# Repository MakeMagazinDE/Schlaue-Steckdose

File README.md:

Maker Media GmbH

***

# Schlaue Steckdose

**Steckdosen, die man über das Handy schalten kann, sind nichts Neues. Auch gibt es Mehrfachsteckdosen, die nur Strom verteilen, wenn ein bestimmtes Gerät an ist. Das alles ist unserem Autor nicht genug und deshalb hat er sich eine Steckdosenleiste gebaut, die Geräte abhängig von seiner Anwesenheit mit Strom versorgt oder bei bestimmten Temperaturen die Heizung regelt.**

Der vollständige Artikel zum Projekt steht in der **[Make-Ausgabe 5/23 ab Seite 54](https://www.heise.de/select/make/2023/5)**.

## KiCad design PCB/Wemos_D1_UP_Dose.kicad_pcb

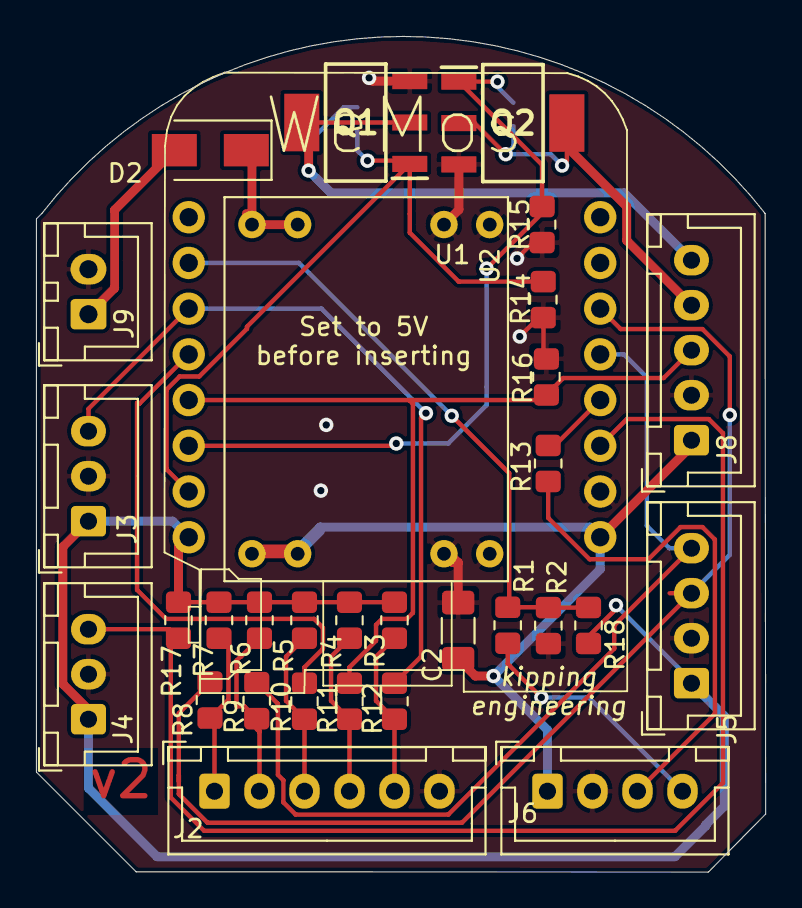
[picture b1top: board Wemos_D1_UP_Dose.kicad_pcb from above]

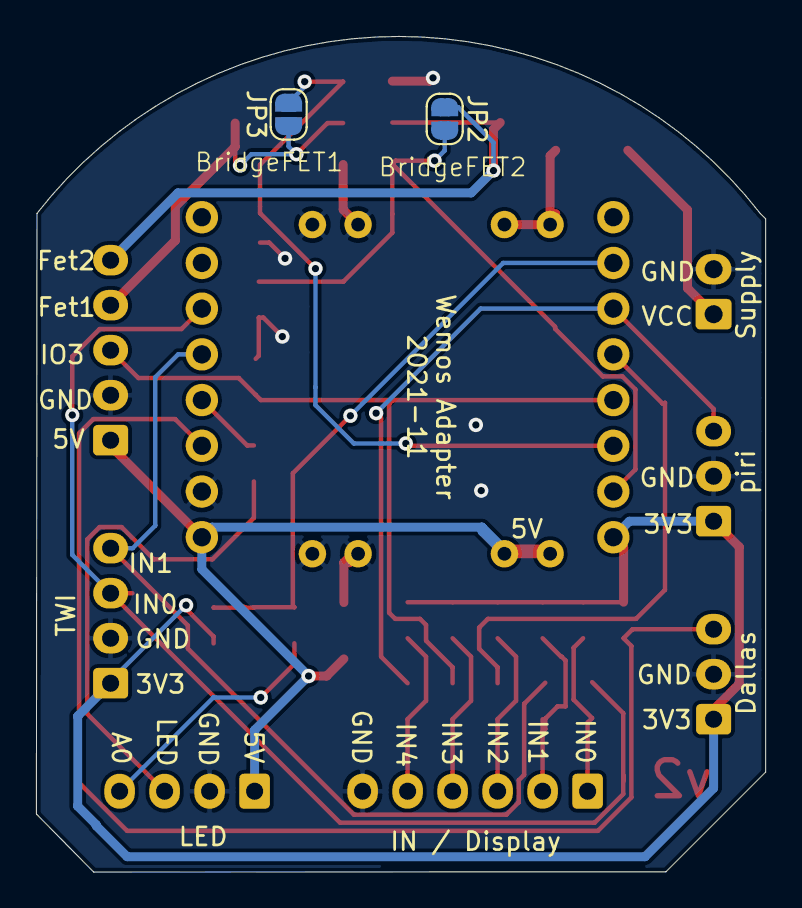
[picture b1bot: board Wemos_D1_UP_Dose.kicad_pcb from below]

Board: 2 copper layers, 40.5 x 46.4 mm, 33 parts (2 on the bottom side), 24 nets.

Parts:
C2: 1µ; C_1206_3216Metric_Pad1.33x1.80mm_HandSolder
D2: US1G; D_SMA
J2: IN_0-4; JST_XH_B6B-XH-A_1x06_P2.50mm_Vertical
J3: IN4_PIRI; JST_XH_B3B-XH-A_1x03_P2.50mm_Vertical
J4: Dallas; JST_XH_B3B-XH-A_1x03_P2.50mm_Vertical
J5: TWI; JST_XH_B4B-XH-A_1x04_P2.50mm_Vertical
J6: LED; JST_XH_B4B-XH-A_1x04_P2.50mm_Vertical
J8: OUT_FET; JST_XH_B5B-XH-A_1x05_P2.50mm_Vertical
J9: POWER; JST_XH_B2B-XH-A_1x02_P2.50mm_Vertical
JP2, JP3: Jumper_NO_Small; SolderJumper-2_P1.3mm_Open_RoundedPad1.0x1.5mm
Q1, Q2: BUK7880-55A_CUX; SOT230P700X180-4N
R1: 100k; R_0805_2012Metric_Pad1.20x1.40mm_HandSolder
R2, R3, R4, R5, R6, R7, R14, R15, R17, R18: 4k7; R_0805_2012Metric_Pad1.20x1.40mm_HandSolder
R8, R9, R10, R11, R12: 1k; R_0805_2012Metric_Pad1.20x1.40mm_HandSolder
R13, R16: 100; R_0805_2012Metric_Pad1.20x1.40mm_HandSolder
U1: WeMos_mini; D1_mini_board
U2: DCDC_1A_Module; DCDC_1A_module

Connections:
+3V3: J3.1, J4.1, J5.1, R3.1, R4.1, R5.1, R6.1, R7.1, R17.2, R18.2, U1.16
+5V: C2.1, J6.1, J8.1, U1.1, U2.2
A0: R1.2, R2.1, R18.1, U1.10
DALLAS: J4.3, R17.1, U1.3
FET_1: JP3.2, Q2.1, R15.1, U1.14
FET_2: JP2.2, Q1.1, R14.1, U1.15
GND: C2.2, J2.6, J3.2, J4.2, J5.2, J6.2, J8.2, J9.2, Q1.3, Q2.3, R2.2, R14.2, R15.2, R16.2, U1.2, U2.3
IN_0: J5.3, R8.2, U1.6
IN_1: J5.4, R9.2, U1.5
IN_2: R10.2, U1.12
IN_3: J8.3, R11.2, R16.1, U1.13
IN_4: J3.3, R12.2, U1.11
LED: R13.2, U1.4
unnamed: D2.1, U2.1
unnamed: D2.2, J9.1
unnamed: J2.1, R7.2, R8.1
unnamed: J2.2, R6.2, R9.1
unnamed: J2.3, R5.2, R10.1
unnamed: J2.4, R4.2, R11.1
unnamed: J2.5, R3.2, R12.1
unnamed: J6.3, R13.1
unnamed: J6.4, R1.1
unnamed: J8.4, JP3.1, Q2.2, Q2.4
unnamed: J8.5, JP2.1, Q1.2, Q1.4

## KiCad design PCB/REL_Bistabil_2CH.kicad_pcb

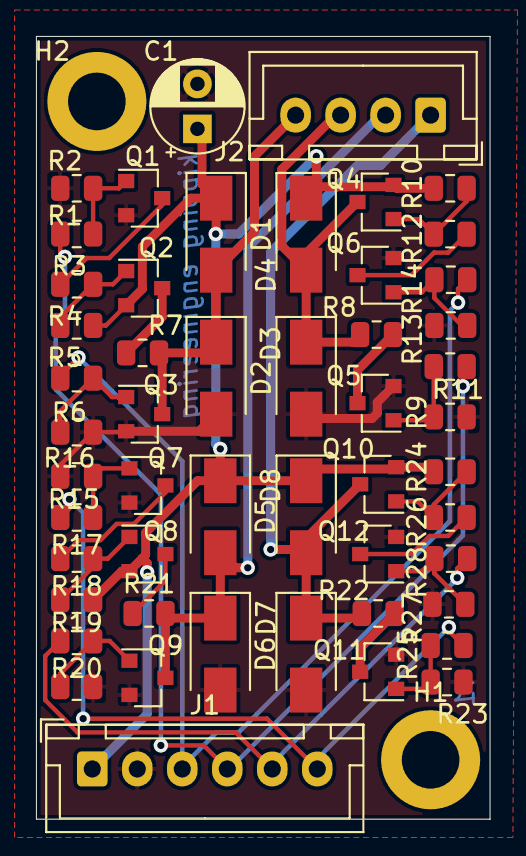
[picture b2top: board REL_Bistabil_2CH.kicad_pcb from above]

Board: 2 copper layers, 25.2 x 43.5 mm, 53 parts (0 on the bottom side), 30 nets.

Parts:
C1: C; CP_Radial_D5.0mm_P2.50mm
D1, D2, D3, D4, D5, D6, D7, D8: US1G; D_SMA
H1, H2: MountingHole; MountingHole_3.2mm_M3_ISO14580_Pad
J1: Conn_01x06_Male; JST_XH_B6B-XH-A_1x06_P2.50mm_Vertical
J2: Conn_01x04_Male; JST_XH_B4B-XH-A_1x04_P2.50mm_Vertical
Q1, Q3, Q5, Q6, Q7, Q9, Q11, Q12: BC817; SOT-23
Q2, Q4, Q8, Q10: BC807; SOT-23
R1, R14, R15, R28: 4k7; R_0805_2012Metric
R2, R4, R6, R9, R10, R13, R16, R18, R20, R23, R24, R27: 100k; R_0805_2012Metric
R3, R12, R17, R26: 1k; R_0805_2012Metric
R5, R11, R19, R25: 200; R_0805_2012Metric
R7, R8, R21, R22: 100; R_0805_2012Metric

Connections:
+12V: C1.1, D1.1, D4.1, D5.1, D8.1, J1.1, Q2.2, Q4.2, Q8.2, Q10.2, R4.1, R10.1, R18.1, R24.1
/h-bridge/REL_R: D3.1, D4.2, J2.3, Q4.3, R8.1
/h-bridge/REL_S: D1.2, D2.1, J2.4, Q3.3, R7.2
/h-bridge/Reset: J1.4, R1.2, R11.2
/h-bridge/Set: J1.3, R5.2, R14.2
/sheet623AF816/REL_R: D7.1, D8.2, J2.1, Q10.3, R22.1
/sheet623AF816/REL_S: D5.2, D6.1, J2.2, Q9.3, R21.2
/sheet623AF816/Reset: J1.6, R15.2, R25.2
/sheet623AF816/Set: J1.5, R19.2, R28.2
GND: C1.2, D2.2, D3.2, D6.2, D7.2, J1.2, Q1.2, Q3.2, Q5.2, Q6.2, Q7.2, Q9.2, Q11.2, Q12.2, R2.2, R6.1, R9.1, R13.2, R16.2, R20.1, R23.1, R27.2
unnamed: Q1.1, R1.1, R2.1
unnamed: Q1.3, R3.2
unnamed: Q2.1, R3.1, R4.2
unnamed: Q2.3, R7.1
unnamed: Q3.1, R5.1, R6.2
unnamed: Q4.1, R10.2, R12.1
unnamed: Q5.1, R9.2, R11.1
unnamed: Q5.3, R8.2
unnamed: Q6.1, R13.1, R14.1
unnamed: Q6.3, R12.2
unnamed: Q7.1, R15.1, R16.1
unnamed: Q7.3, R17.2
unnamed: Q8.1, R17.1, R18.2
unnamed: Q8.3, R21.1
unnamed: Q9.1, R19.1, R20.2
unnamed: Q10.1, R24.2, R26.1
unnamed: Q11.1, R23.2, R25.1
unnamed: Q11.3, R22.2
unnamed: Q12.1, R27.1, R28.1
unnamed: Q12.3, R26.2
